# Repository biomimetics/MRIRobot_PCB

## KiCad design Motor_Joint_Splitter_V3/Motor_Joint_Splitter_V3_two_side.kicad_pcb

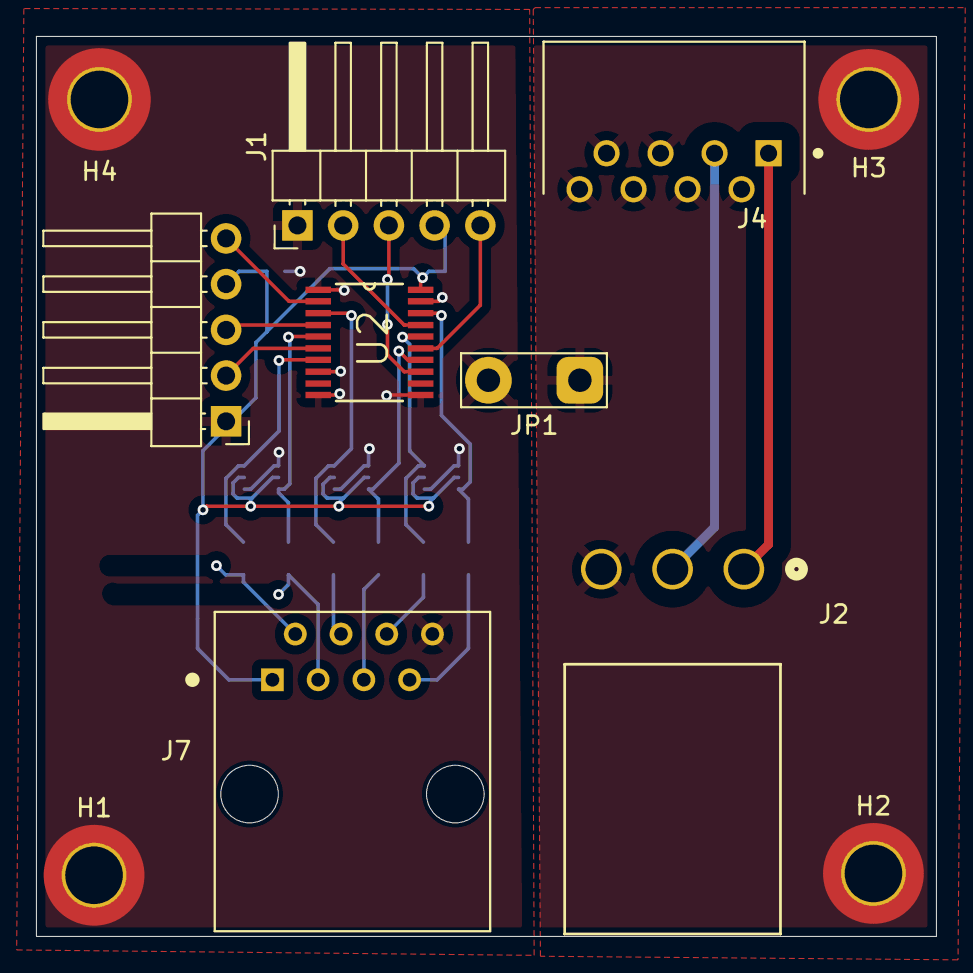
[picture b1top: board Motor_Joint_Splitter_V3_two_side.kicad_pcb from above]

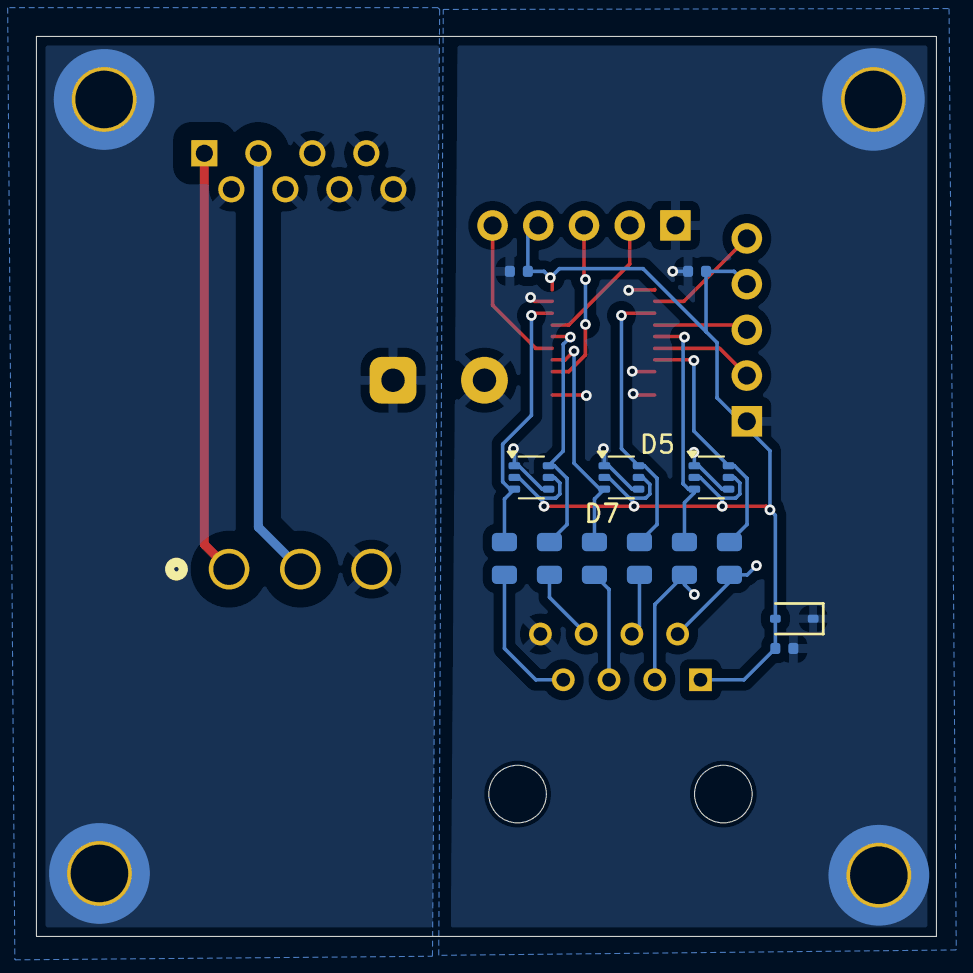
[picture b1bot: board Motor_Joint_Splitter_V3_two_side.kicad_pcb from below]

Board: 2 copper layers, 50.0 x 50.0 mm, 24 parts (13 on the bottom side), 23 nets.

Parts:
C1, C3, C4: 1uF; C_0402
D4: H5VHD3BC; D_SOD-323
D5, D6, D7: BAT54SDW; SOT-363_SC-70-6
H1, H2, H3: MountingHole_Pad; MountingHole_3.2mm_M3_DIN965_Pad_TopBottom
H4: MountingHole_Pad; MountingHole_3.2mm_M3_ISO7380_Pad_TopBottom
J1, J9: Conn_01x05; PinHeader_1x05_P2.54mm_Horizontal
J2: 26605030; CONN_SDA-41792_M450_03_MOL
J4: motor_connector_292206-8; TE_292206-8
J7: ethernet_54602-908LF; AMPHENOL_54602-908LF
JP1: Jumper_2_Open; TestPoint_2Pads_Pitch5.08mm_Drill1.3mm
R13, R14, R15, R16, R17, R19: 120Ω; R_0805
U2: 74ACT244MTCX; line_driver_SOP65P640X120-20N

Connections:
+5V: C1.2, C3.1, C4.1, D4.2, D5.2 (K), D5.5 (K), D6.2 (K), D6.5 (K), D7.2 (K), D7.5 (K), J1.4, J7.1, J9.4, U2.20 (VCC)
/C_A: J1.3, U2.13 (I6)
/C_A_Out: D5.6 (K), R19.1, U2.7 (O6)
/C_A_Out_2: J7.2, R19.2
/C_B: J1.5, U2.15 (I5)
/C_B_Out: D5.3 (K), R13.1, U2.5 (O5)
/C_B_Out_2: J7.3, R13.2
/C_I: J1.2, U2.17 (I4)
/C_I_Out: D7.6 (A), R14.1, U2.3 (O4)
/C_I_Out_2: J7.4, R14.2
/Cos: J2.2, J4.3
/SEA_A: J9.3, U2.4 (I1)
/SEA_A_Out: D6.6 (A), R15.1, U2.16 (O1)
/SEA_A_Out_2: J7.6, R15.2
/SEA_B: J9.5, U2.2 (I0)
/SEA_B_Out: D6.3 (A), R16.1, U2.18 (O0)
/SEA_B_Out_2: J7.7, R16.2
/SEA_I: J9.2, U2.6 (I2)
/SEA_I_Out: D7.3 (A), R17.1, U2.14 (O2)
/SEA_I_Out_2: J7.5, R17.2
/Sin: J2.1, J4.1
GND: C1.1, C3.2, C4.2, D4.1, D5.1 (A), D5.4 (A), D6.1 (A), D6.4 (A), D7.1 (A), D7.4 (A), H1.1, H4.1, J1.1, J7.8, J9.1, JP1.2 (B), U2.1 (~OE1), U2.8 (I3), U2.10 (GND), U2.11 (I7), U2.19 (~OE2)
GND_M: H2.1, H3.1, J2.3, J4.2, J4.4, J4.5, J4.6, J4.7, J4.8, JP1.1 (A)

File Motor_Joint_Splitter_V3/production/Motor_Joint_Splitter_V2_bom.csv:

"Reference","Value","Datasheet","Footprint","Qty","DNP","LCSC"
"C3,C4","1uF","https://www.lcsc.com/datasheet/lcsc_datasheet_2304140030_Sam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","PCM_JLCPCB:C_0402","2","","C52923"
"D4","H5VHD3BC","https://wmsc.lcsc.com/wmsc/upload/file/pdf/v2/lcsc/240126152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","PCM_JLCPCB:D_SOD-323","1","","C20615804"
"D5,D6,D7","BAT54SDW","https://www.diodes.com/assets/Datasheets/BAT54TW_ADW_CDW_SDW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","Package_TO_SOT_SMD:SOT-363_SC-70-6","3","","C77323"
"J2","26605030","https://www.molex.com/en-us/products/part-detail-pdf/2660503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","CONN_SDA-41792_M450_03_MOL","1","","C587093"
"J7","ethernet_54602-908LF","https://cdn.amphenol-cs.com/media/wysiwyg/files/documentatio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","splitter_parts:AMPHENOL_54602-908LF","1","","C2847314"
"J8","motor_connector_292206-8","","splitter_parts:TE_292206-8","1","","C591662"
"J9","Conn_01x05","~","Connector_PinHeader_2.54mm:PinHeader_1x05_P2.54mm_Horizontal","1","",""
"R13,R14,R15,R16,R17,R19","120Ω","https://www.lcsc.com/datasheet/lcsc_datasheet_2206010216_UNI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","PCM_JLCPCB:R_0805","6","","C17437"
"U2","74ACT244MTCX","","splitter_parts:line_driver_SOP65P640X120-20N","1","","C5496"

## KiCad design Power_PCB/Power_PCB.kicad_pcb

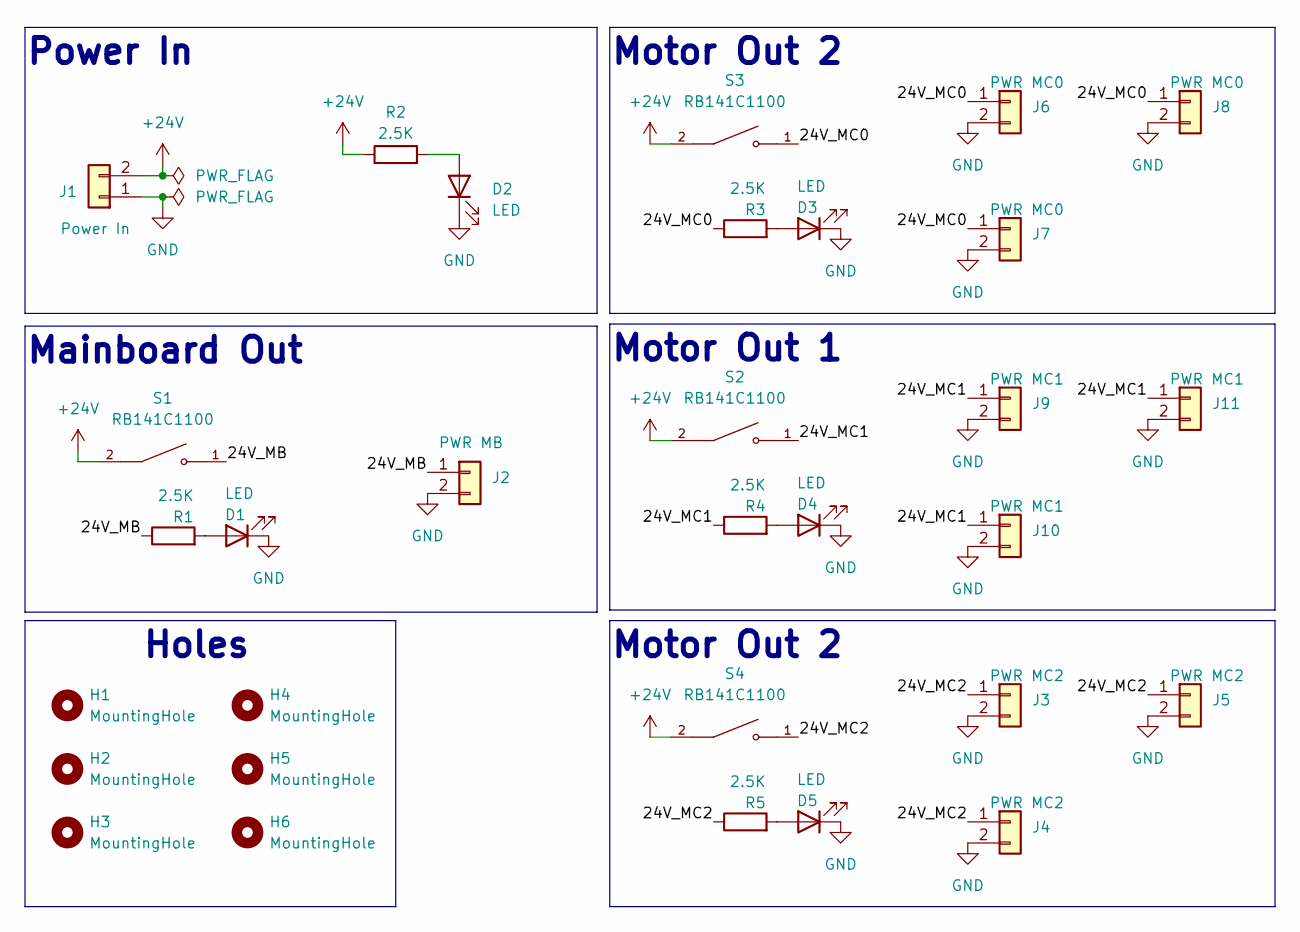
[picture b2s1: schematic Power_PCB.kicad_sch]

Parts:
D1, D2, D3, D4, D5: LED; LED_0805_2012Metric
H1, H2, H3, H4, H5, H6: MountingHole; MountingHole_3.2mm_M3
J1: Power In; AMASS_XT60-M_1x02_P7.20mm_Vertical
J2: PWR MB; AMASS_XT60-M_1x02_P7.20mm_Vertical
J3, J4, J5: PWR MC2; AMASS_XT30U-M_1x02_P5.0mm_Vertical
J6, J7, J8: PWR MC0; AMASS_XT30U-M_1x02_P5.0mm_Vertical
J9, J10, J11: PWR MC1; AMASS_XT30U-M_1x02_P5.0mm_Vertical
R1, R2, R3, R4, R5: 2.5K; R_0805_2012Metric
S1, S2, S3, S4: RB141C1100; SW_RB141C1100; PARTREV C

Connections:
+24V: J1.2, R2.1, S1.2, S2.2, S3.2, S4.2
/24V_MB: J2.1, R1.1, S1.1
/24V_MC0: J6.1, J7.1, J8.1, R3.1, S3.1
/24V_MC1: J9.1, J10.1, J11.1, R4.1, S2.1
/24V_MC2: J3.1, J4.1, J5.1, R5.1, S4.1
GND: D1.1 (K), D2.1 (K), D3.1 (K), D4.1 (K), D5.1 (K), J1.1, J2.2, J3.2, J4.2, J5.2, J6.2, J7.2, J8.2, J9.2, J10.2, J11.2
unnamed: D1.2 (A), R1.2
unnamed: D2.2 (A), R2.2
unnamed: D3.2 (A), R3.2
unnamed: D4.2 (A), R4.2
unnamed: D5.2 (A), R5.2

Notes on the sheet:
Power In
Motor Out 2
Holes
Motor Out 1
Mainboard Out

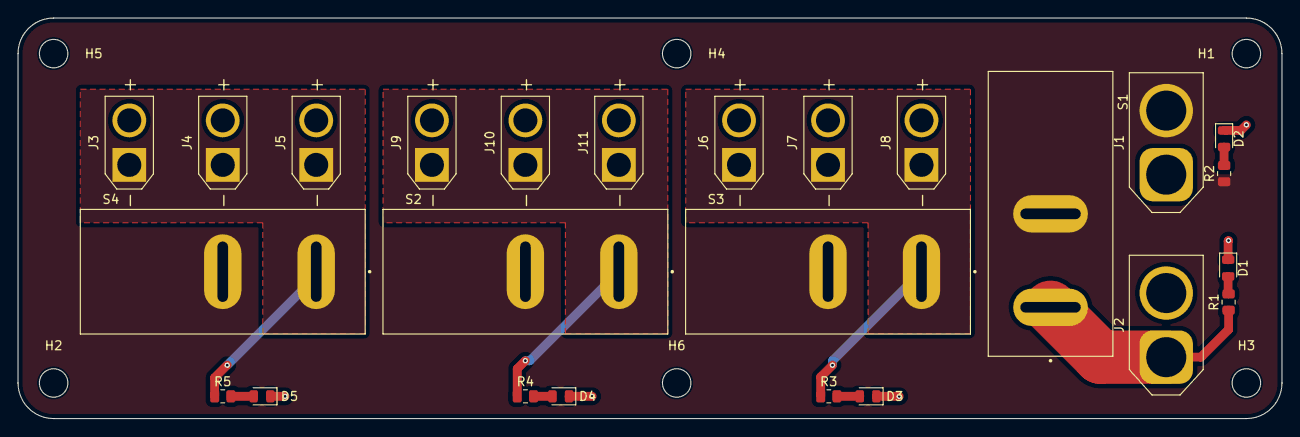
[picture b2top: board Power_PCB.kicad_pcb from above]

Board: 2 copper layers, 142.0 x 45.0 mm, 31 parts (0 on the bottom side), 11 nets.
